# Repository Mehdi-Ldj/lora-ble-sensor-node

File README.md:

# Off-Grid Agricultural LoRa/BLE Sensor Node — Rev A

A 55 mm round, four-layer sensor node that runs from a solar cell and a 14500
LiFePO4 cell: 868 MHz LoRa, 2.4 GHz BLE, and an environmental sensor suite on
one board.

## Design viewer

| Schematic | Board |
|:---:|:---:|
| [Schematic, six pages (PDF)](docs/renders/schematic-rev-a.pdf) | [Open the project in KiCanvas][kicanvas] |

KiCanvas loads the whole project in the browser: the board opens first, and the
five sheets are one click away in its Project panel. No KiCad installation
required. The PDF is the quickest way to read the schematic end to end.

[kicanvas]: https://kicanvas.org/?repo=https%3A%2F%2Fgithub.com%2FMehdi-Ldj%2Flora-ble-sensor-node%2Ftree%2Fmain%2Fhardware%2Frev-a

## Overview

The node is meant to sit in a field and report microclimate data for months at a
time without a battery change. A solar harvester tops up a single LiFePO4 cell,
a boost holds 3.3 V, and the MCU wakes to sample temperature, humidity and soil
moisture before transmitting over LoRa.

Three choices shaped the board more than anything else:

- The radio is split. A bare nRF52840 runs BLE from a PCB antenna, while an
  SX1262 carries the long-range link through a U.FL connector, so the 868 MHz
  front end can be measured and re-matched without touching the MCU.
- The MCU is a bare aQFN73 at 0.4 mm pitch, fanned out directly on the top
  layer. No module, no fanout board.
- The RF feed is impedance-controlled. The 868 MHz path, the 2.4 GHz antenna
  feed and the U.FL launch all run in a 50 Ω net class over an In1.Cu plane, on
  a stackup chosen for that geometry.

The outline is the last constraint: Ø55 mm, three mounting holes, and an antenna
keepout that no layer may cross.

## Features

- **868 MHz** LoRa, discrete SX1262 with a switchless match/filter/balun and a
  U.FL measurement point
- **2.4 GHz** BLE from a bare **nRF52840** (aQFN73) with an on-board PCB antenna
- **BQ25570** solar harvester with PMOS reverse-polarity protection and TVS
- **TPS61099** 3.3 V boost from a single-cell 14500 LiFePO4
- Battery PTC, reverse-polarity protection, current-measure jumper and NTC divider
- **BME280** environment sensor and a switched analog soil probe
- SWD debug header, six test points, three fiducials
- 96 parts across five hierarchical sheets

## Board specifications

| Item | Value |
|---|---|
| Board size | **Ø 55.0 mm**, 4 layers |
| Stackup | **JLC04161H-7628**, FR4, Er 4.6, 1.6 mm nominal |
| Copper | 1 oz outer and inner, ENIG finish, green mask, white silk |
| Minimum feature | 0.20 mm track, 0.15 mm clearance, 0.20 mm drill |
| Vias | 0.30/0.20 mm and 0.20/0.20 mm, tented, no blind or buried |
| Impedance | 50 Ω ±10 % single-ended, In1.Cu reference |
| Assembly | JLCPCB Standard PCBA, 2 prototypes |

## Architecture

Line colour and weight separate the five signal classes: power, digital, analog,
RF and control. The 3V3 bus feeds the radio and the sensing block from the same
boost converter, and the soil probe is switched so it draws nothing while the
node sleeps.

## Design notes

### 868 MHz feed

The radio sheet carries a switchless match, filter and balun between the SX1262
and the U.FL, laid out as a 50 Ω coplanar waveguide over the In1.Cu ground plane.
The geometry was chosen from a quasi-static 2D sweep before layout:

| W (mm) | S (mm) | h (mm) | Z₀ (Ω) | εeff |
|---:|---:|---:|---:|---:|
| 0.38 | 0.20 | 0.210 | **50.4** | 3.51 |

The sweep and its caveats are in
[`simulation/results/cpw_sweep.md`](simulation/results/cpw_sweep.md). The
full-wave model and the VNA coupon are still to be run.

### 2.4 GHz antenna

The PCB antenna sits in a keepout with no copper on any layer, fed from the
nRF52840 through the same 50 Ω class. The keepout is the fragile part, and it is
documented with the stackup in [`docs/stackup.md`](docs/stackup.md).

### Power

The BQ25570 runs as a boost charger only — its buck converter is deliberately
unused — feeding a single LiFePO4 cell through a PTC and a reverse-polarity
PMOS. The TPS61099 then holds 3.3 V for the MCU, radio and sensors, and the soil
probe is switched so it cannot leak current while the node sleeps. The full pin
list and the reviewed net table are in the schematic.

### Package and assembly

Four layers carry the aQFN73 fanout on the top, a solid ground below it, and the
supplies on the inner layers. Assembly is Standard PCBA with X-ray, because the
aQFN73 and the BME280 both have pads underneath.

## Layout

| Front copper | Back copper |
|:---:|:---:|
|  |  |
| **Inner 1 — ground plane** | **Inner 2 — power** |
|  |  |

## Repository structure

| Path | Contents |
|---|---|
| `hardware/rev-a/` | KiCad 10 project: five schematic sheets, PCB, symbol and footprint libraries, 3D models |
| `simulation/` | Coplanar-waveguide pre-check for the 868 MHz feed, and the plan for the 3D model |
| `docs/` | [Assembly](docs/assembly-notes.md), [fabrication](docs/fab-notes.md) and [PCBA](docs/pcba-notes.md) notes, [stackup](docs/stackup.md), [impedance](docs/impedance.md), schematic PDF |
| `firmware/` | Reserved for the node firmware |

Open the project with KiCad 10:

```bash
kicad hardware/rev-a/lora-node.kicad_pro
```

## Fabrication and assembly

The board is drawn for JLCPCB 4-layer fabrication and Standard PCBA, with X-ray
inspection for the aQFN73 and BME280. Paste, stencil and panel choices are in
[`docs/fab-notes.md`](docs/fab-notes.md),
[`docs/assembly-notes.md`](docs/assembly-notes.md) and
[`docs/pcba-notes.md`](docs/pcba-notes.md).

The fabrication package for a release — gerbers, drill file, job file, BOM and
CPL — is attached to the release rather than committed here.

## Status

**Rev A is frozen and has not been fabricated yet.** The design is complete
through DRC, ERC and schematic/board parity.

## Licence

Released under the [CERN Open Hardware Licence Version 2 – Permissive](LICENSE).

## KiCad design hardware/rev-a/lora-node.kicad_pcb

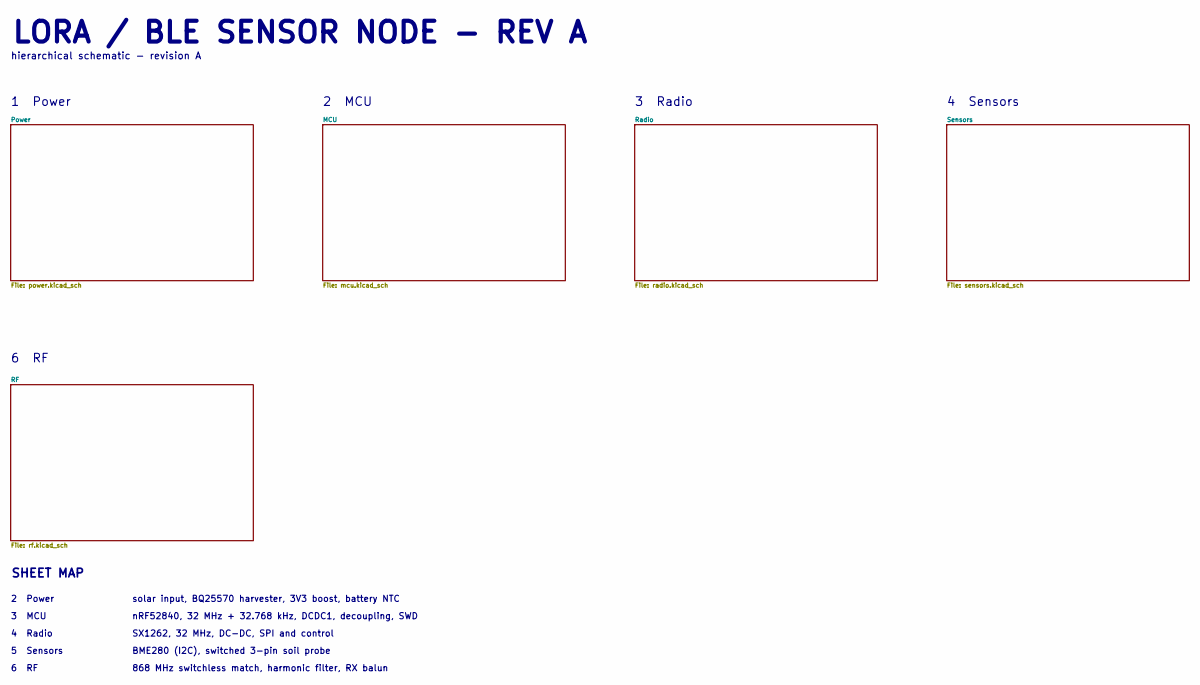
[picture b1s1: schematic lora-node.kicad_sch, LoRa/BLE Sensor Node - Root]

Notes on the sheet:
5 Sensors
4 Radio
2 MCU
3 MCU
2 Power
6 RF
SHEET MAP
BME280 (I2C), switched 3-pin soil probe
SX1262, 32 MHz, DC-DC, SPI and control
hierarchical schematic - revision A
LORA / BLE SENSOR NODE - REV A
1 Power
solar input, BQ25570 harvester, 3V3 boost, battery NTC
3 Radio
868 MHz switchless match, harmonic filter, RX balun
4 Sensors
nRF52840, 32 MHz + 32.768 kHz, DCDC1, decoupling, SWD

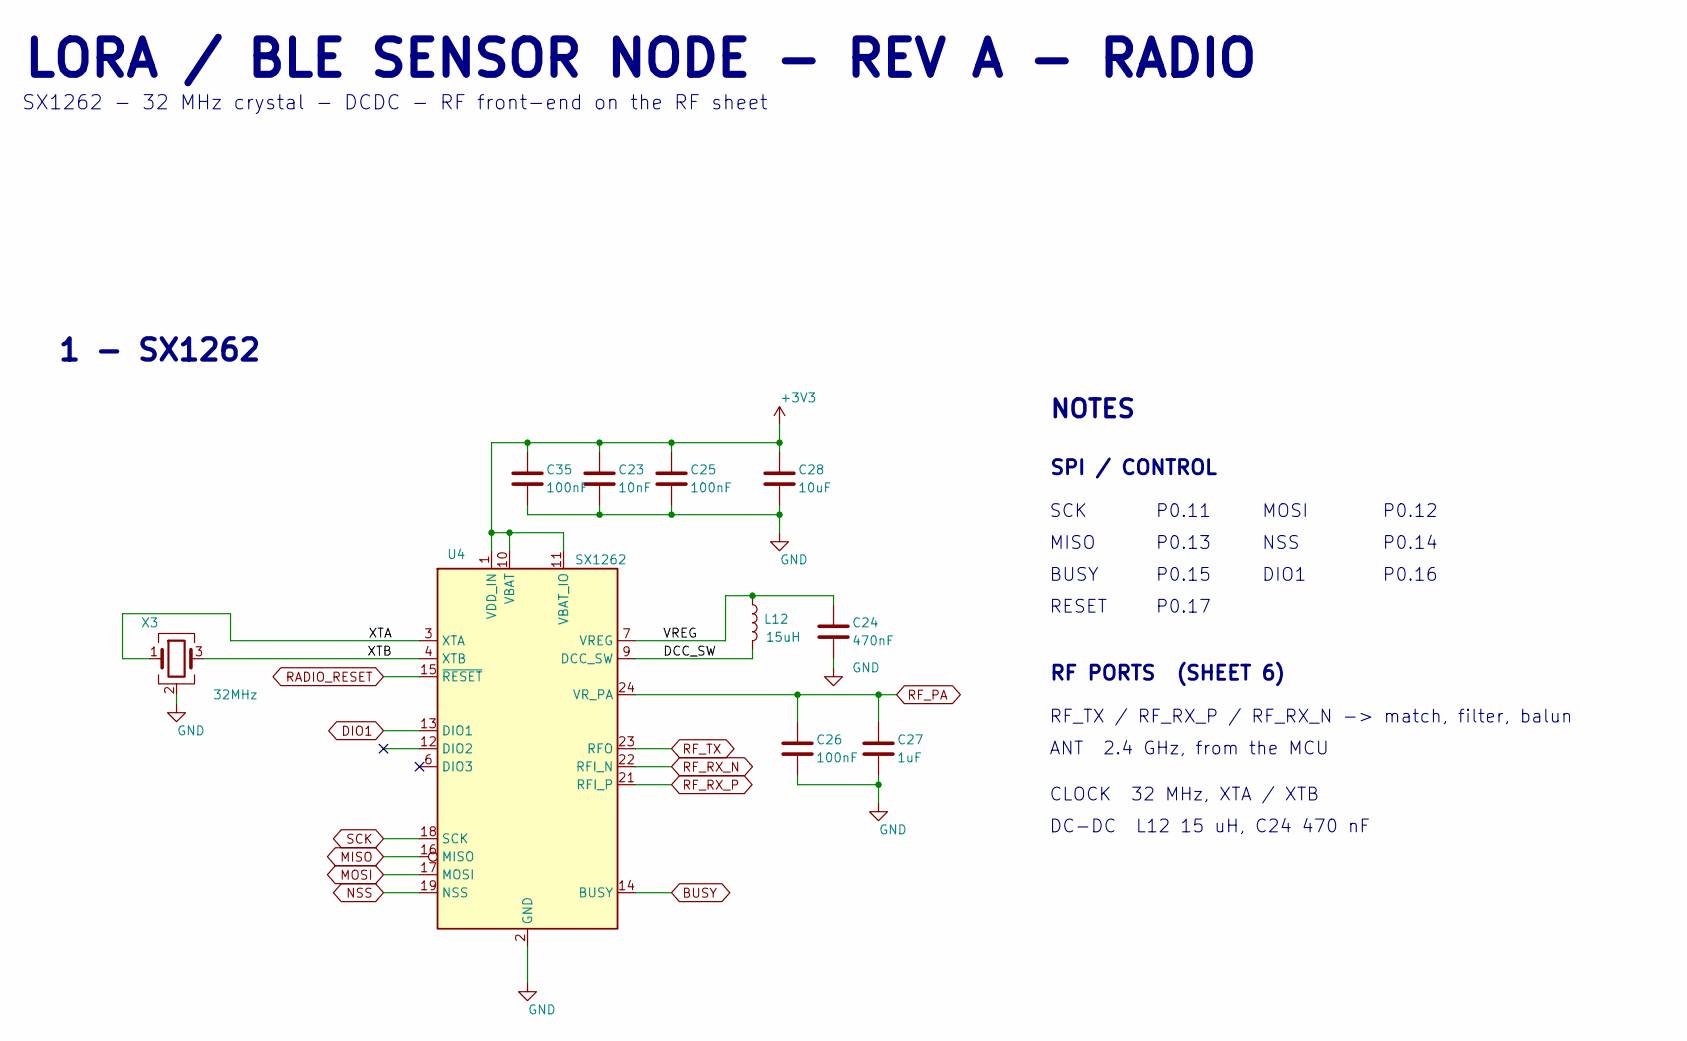
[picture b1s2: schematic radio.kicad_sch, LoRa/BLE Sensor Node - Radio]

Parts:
C23: 10nF; C_0402_1005Metric; MPN CL05B103KB5NNNC; LCSC C15195
C24: 470nF; C_0402_1005Metric; MPN CL05A474KP5NNNC; LCSC C47339
C25, C26, C35: 100nF; C_0402_1005Metric; MPN CL05B104KO5NNNC; LCSC C1525
C27: 1uF; C_0603_1608Metric; MPN CL10B105KA8NNNC; LCSC C29936
C28: 10uF; C_0805_2012Metric; MPN CL21A106KAYNNNE; LCSC C15850
L12: 15uH; L_0603_1608Metric; MPN MGFL1608F150MT-LF; LCSC C486329
U4: SX1262; QFN-24-1EP_4x4mm_P0.5mm_EP2.6x2.6mm; MPN SX1262IMLTRT; LCSC C191341
X3: 32MHz; Crystal_SMD_2016-4Pin_2.0x1.6mm; MPN ECS-320-10-37B-CKY-TR; LCSC C2450496

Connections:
+3V3: C23.1, C25.1, C28.1, C35.1, U4.1 (VDD_IN), U4.10 (VBAT), U4.11 (VBAT_IO); also elsewhere on the board
/Radio/DCC_SW: L12.2, U4.9 (DCC_SW)
/Radio/VREG: C24.1, L12.1, U4.7 (VREG)
/Radio/XTA: U4.3 (XTA), X3.1
/Radio/XTB: U4.4 (XTB), X3.3
BUSY: U4.14 (BUSY); also elsewhere on the board
DIO1: U4.13 (DIO1); also elsewhere on the board
GND: C23.2, C24.2, C25.2, C26.2, C27.2, C28.2, C35.2, U4.2 (GND), U4.5 (GND), U4.8 (GND), U4.20 (GND), U4.25 (GND), X3.2 (G), X3.4 (G); also elsewhere on the board
MISO: U4.16 (MISO); also elsewhere on the board
MOSI: U4.17 (MOSI); also elsewhere on the board
NSS: U4.19 (NSS); also elsewhere on the board
RADIO_RESET: U4.15 (~RESET); also elsewhere on the board
RF_PA: C26.1, C27.1, U4.24 (VR_PA); also elsewhere on the board
RF_RX_N: U4.22 (RFI_N); also elsewhere on the board
RF_RX_P: U4.21 (RFI_P); also elsewhere on the board
RF_TX: U4.23 (RFO); also elsewhere on the board
SCK: U4.18 (SCK); also elsewhere on the board

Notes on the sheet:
SPI / CONTROL
P0.11
DIO1
RF PORTS (SHEET 6)
1 - SX1262
CLOCK 32 MHz, XTA / XTB
DC-DC L12 15 uH, C24 470 nF
NSS
NOTES
BUSY
MOSI
LORA / BLE SENSOR NODE - REV A - RADIO
P0.16
SCK
SX1262 - 32 MHz crystal - DCDC - RF front-end on the RF sheet
P0.17
RF_TX / RF_RX_P / RF_RX_N -> match, filter, balun
P0.15
RESET
ANT 2.4 GHz, from the MCU
P0.12
P0.13
MISO
P0.14

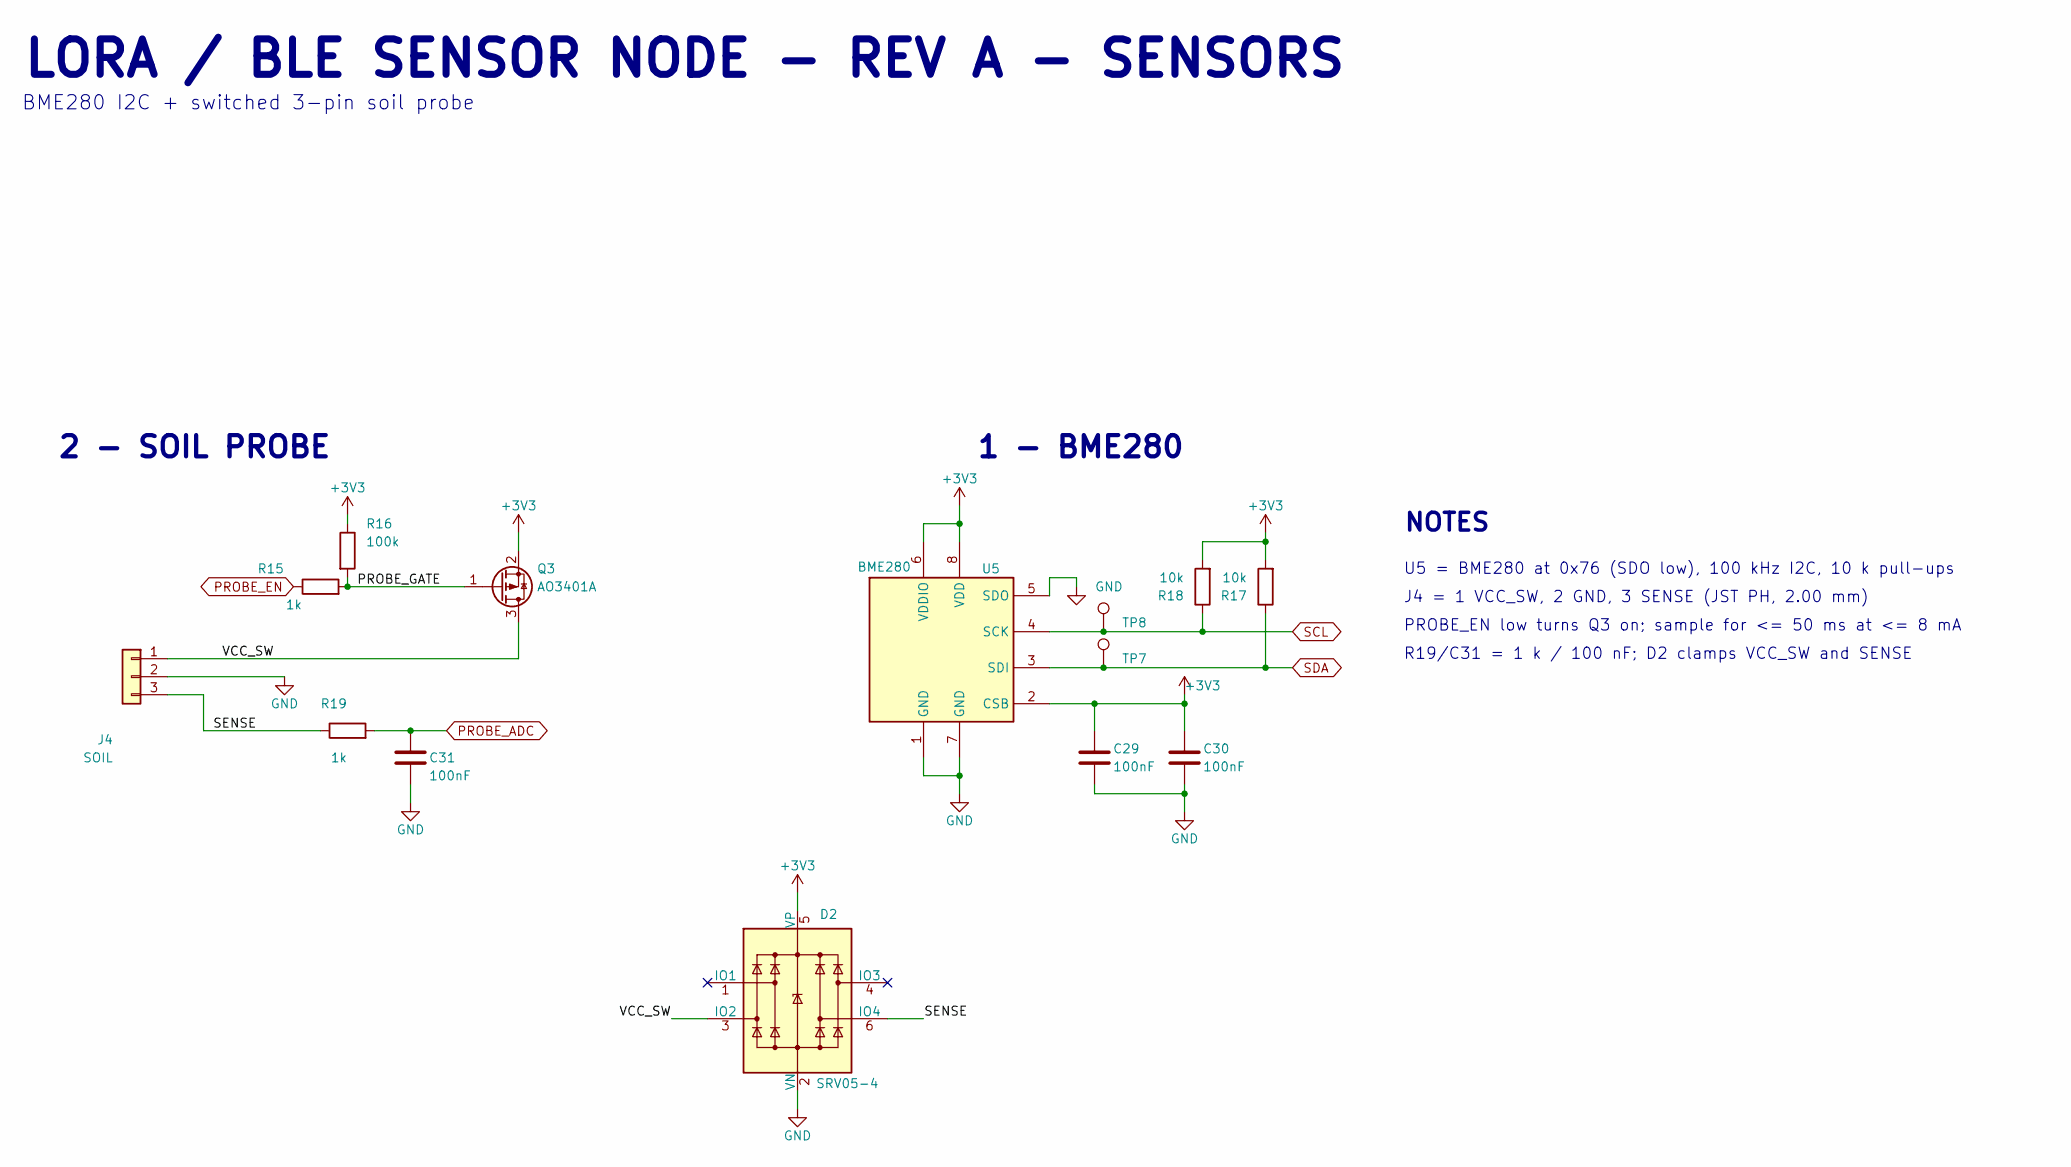
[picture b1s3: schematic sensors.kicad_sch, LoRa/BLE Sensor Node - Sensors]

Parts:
C29, C30, C31: 100nF; C_0402_1005Metric; MPN CL05B104KO5NNNC; LCSC C1525
D2: SRV05-4; SOT-23-6; MPN SRV05-4.TCT; LCSC C13612
J4: SOIL; JST_PH_B3B-PH-K_1x03_P2.00mm_Vertical; MPN B3B-PH-K-S(LF)(SN); LCSC C131339
Q3: AO3401A; SOT-23; MPN AO3401A; LCSC C15127
R15, R19: 1k; R_0402_1005Metric; MPN 0402WGF1001TCE; LCSC C11702
R16: 100k; R_0402_1005Metric; MPN 0402WGF1003TCE; LCSC C25741
R17, R18: 10k; R_0402_1005Metric; MPN RC0402FR-0710KL; LCSC C60490
TP7: SDA; TestPoint_Pad_D1.0mm
TP8: SCL; TestPoint_Pad_D1.0mm
U5: BME280; Bosch_LGA-8_2.5x2.5mm_P0.65mm_ClockwisePinNumbering; MPN BME280; LCSC C92489

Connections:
+3V3: C29.1, C30.1, D2.5 (VP), Q3.2 (S), R16.1, R17.2, R18.2, U5.2 (CSB), U5.6 (VDDIO), U5.8 (VDD); also elsewhere on the board
/Sensors/PROBE_GATE: Q3.1 (G), R15.2, R16.2
/Sensors/SENSE: D2.6 (IO4), J4.3, R19.1
/Sensors/VCC_SW: D2.3 (IO2), J4.1, Q3.3 (D)
GND: C29.2, C30.2, C31.2, D2.2 (VN), J4.2, U5.1 (GND), U5.5 (SDO), U5.7 (GND); also elsewhere on the board
PROBE_ADC: C31.1, R19.2; also elsewhere on the board
PROBE_EN: R15.1; also elsewhere on the board
SCL: R18.1, TP8.1 (1_1), U5.4 (SCK); also elsewhere on the board
SDA: R17.1, TP7.1 (1_1), U5.3 (SDI); also elsewhere on the board

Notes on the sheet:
J4 = 1 VCC_SW, 2 GND, 3 SENSE (JST PH, 2.00 mm)
LORA / BLE SENSOR NODE - REV A - SENSORS
BME280 I2C + switched 3-pin soil probe
1 - BME280
NOTES
U5 = BME280 at 0x76 (SDO low), 100 kHz I2C, 10 k pull-ups
2 - SOIL PROBE
PROBE_EN low turns Q3 on; sample for <= 50 ms at <= 8 mA
R19/C31 = 1 k / 100 nF; D2 clamps VCC_SW and SENSE

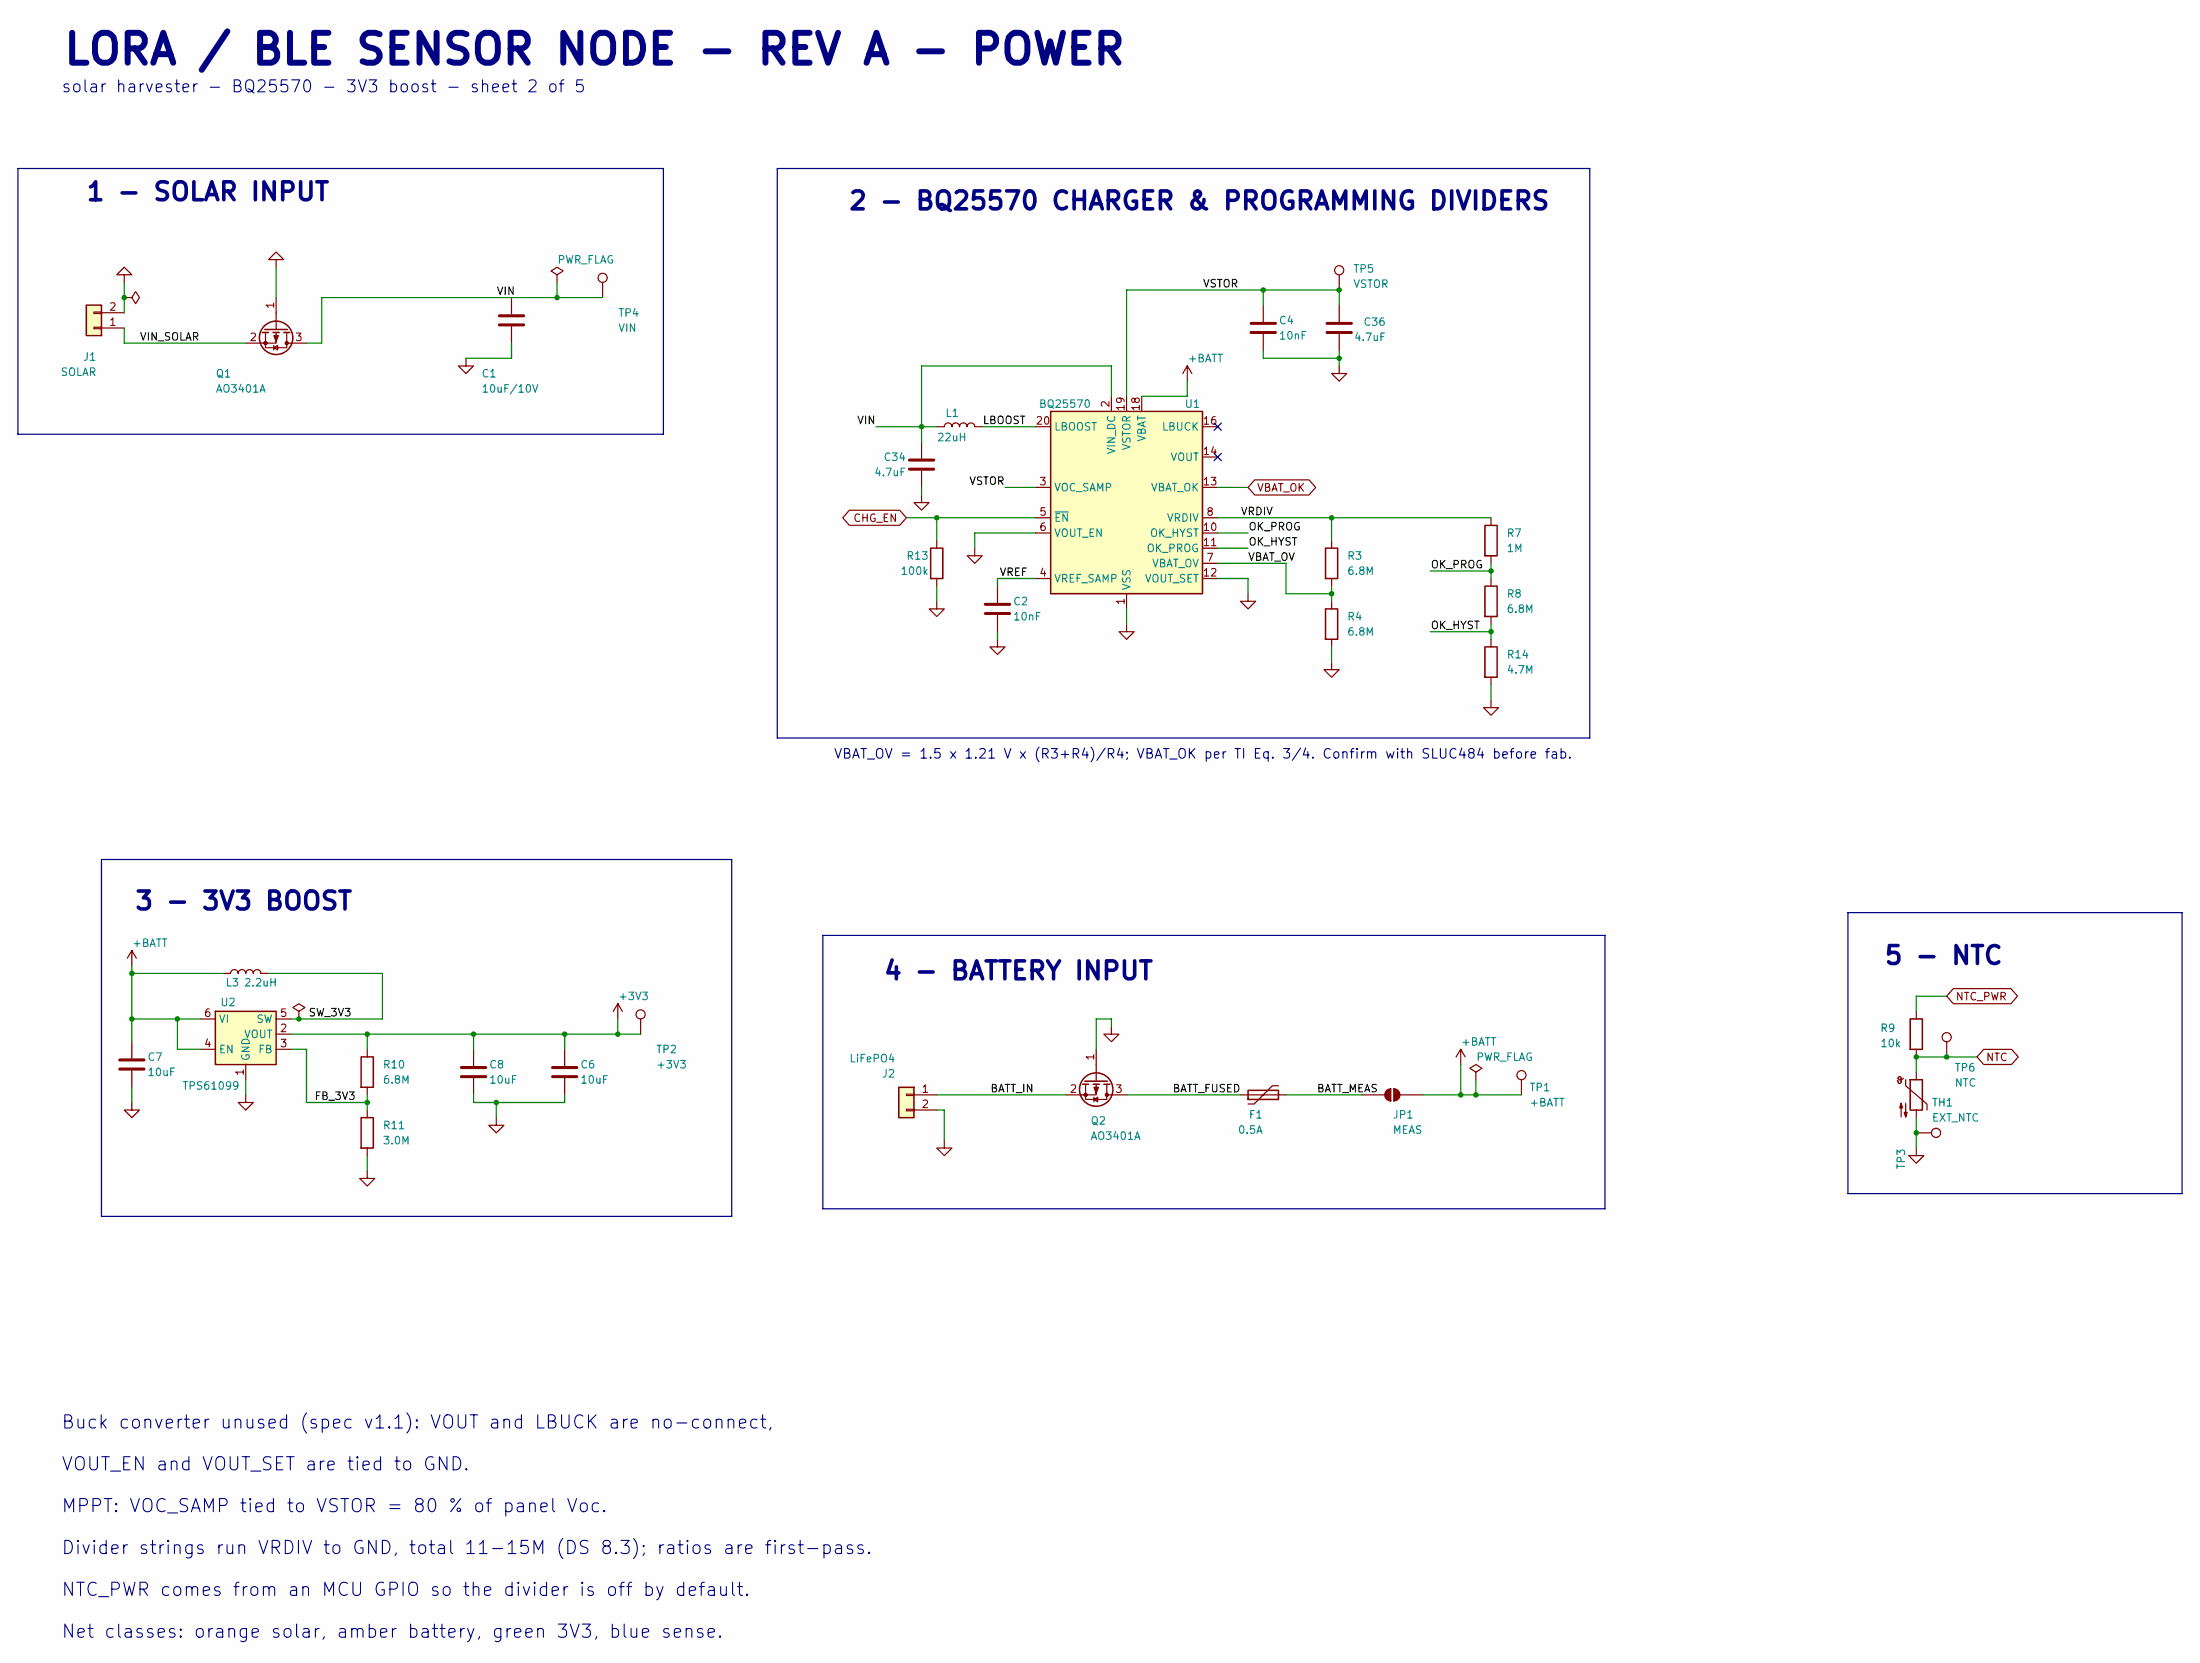
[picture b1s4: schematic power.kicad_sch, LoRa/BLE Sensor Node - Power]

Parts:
C1: 10uF/10V; C_0805_2012Metric; MPN CL21A106KAYNNNE; LCSC C15850
C2, C4: 10nF; C_0402_1005Metric; MPN CL05B103KB5NNNC; LCSC C15195
C6, C7, C8: 10uF; C_0805_2012Metric; MPN CL21A106KAYNNNE; LCSC C15850
C34, C36: 4.7uF; C_0603_1608Metric; MPN CL10A475KO8NNNC; LCSC C19666
F1: 0.5A; Fuse_1812_4532Metric; MPN SMD1812P050TF/30; LCSC C12559
J1: SOLAR; JST_PH_B2B-PH-K_1x02_P2.00mm_Vertical; MPN B2B-PH-K-S(LF)(SN); LCSC C131337
J2: LiFePO4; JST_PH_B2B-PH-K_1x02_P2.00mm_Vertical; MPN B2B-PH-K-S(LF)(SN); LCSC C131337
JP1: MEAS; PinHeader_1x02_P2.54mm_Vertical; MPN PZ254V-11-02P; LCSC C492401
L1: 22uH; L_1210_3225Metric; MPN CBC3225T220KR; LCSC C223225
L3: 2.2uH; L_1210_3225Metric; MPN DFE322512F-2R2M=P2; LCSC C3222669
Q1, Q2: AO3401A; SOT-23; MPN AO3401A; LCSC C15127
R3, R4, R8, R10: 6.8M; R_0402_1005Metric; MPN RC0402FR-076M8L; LCSC C477777
R7: 1M; R_0402_1005Metric; MPN 0402WGF1004TCE; LCSC C26083
R9: 10k; R_0402_1005Metric; MPN RC0402FR-0710KL; LCSC C60490
R11: 3.0M; R_0402_1005Metric; MPN 0402WGF3004TCE; LCSC C56582
R13: 100k; R_0402_1005Metric; MPN 0402WGF1003TCE; LCSC C25741
R14: 4.7M; R_0402_1005Metric; MPN 0402WGF4704TCE; LCSC C474132
TH1: EXT_NTC; JST_XH_B2B-XH-A_1x02_P2.50mm_Vertical; MPN B2B-XH-A(LF)(SN); LCSC C158012
TP1: +BATT; TestPoint_Pad_D1.0mm
TP2: +3V3; TestPoint_Pad_D1.0mm
TP3: TestPoint_Pad_D1.0mm
TP4: VIN; TestPoint_Pad_D1.0mm
TP5: VSTOR; TestPoint_Pad_D1.0mm
TP6: NTC; TestPoint_Pad_D1.0mm
U1: BQ25570; QFN-20-1EP_3.5x3.5mm_P0.5mm_EP2x2mm; MPN BQ25570RGRR; LCSC C506250
U2: TPS61099; WSON-6-1EP_2x2mm_P0.65mm_EP1x1.6mm; MPN TPS61099DRVR; LCSC C2842395

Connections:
+3V3: C6.1, C8.1, R10.1, TP2.1 (1_1), U2.2 (VOUT); also elsewhere on the board
+BATT: C7.1, JP1.2 (B), L3.1, TP1.1 (1_1), U1.18 (VBAT), U2.4 (EN), U2.6 (VI)
/Power/BATT_FUSED: F1.1, Q2.3 (D)
/Power/BATT_IN: J2.1, Q2.2 (S)
/Power/BATT_MEAS: F1.2, JP1.1 (A)
/Power/FB_3V3: R10.2, R11.1, U2.3 (FB)
/Power/LBOOST: L1.2, U1.20 (LBOOST)
/Power/OK_HYST: R8.2, R14.1, U1.11 (OK_PROG)
/Power/OK_PROG: R7.2, R8.1, U1.10 (OK_HYST)
/Power/SW_3V3: L3.2, U2.5 (SW)
/Power/VBAT_OV: R3.2, R4.1, U1.7 (VBAT_OV)
/Power/VIN: C1.1, C34.1, L1.1, Q1.3 (D), TP4.1 (1_1), U1.2 (VIN_DC)
/Power/VIN_SOLAR: J1.1, Q1.2 (S)
/Power/VRDIV: R3.1, R7.1, U1.8 (VRDIV)
/Power/VREF: C2.1, U1.4 (VREF_SAMP)
/Power/VSTOR: C4.1, C36.1, TP5.1 (1_1), U1.3 (VOC_SAMP), U1.19 (VSTOR)
CHG_EN: R13.1, U1.5 (~EN); also elsewhere on the board
GND: C1.2, C2.2, C4.2, C6.2, C7.2, C8.2, C34.2, C36.2, J1.2, J2.2, Q1.1 (G), Q2.1 (G), R4.2, R11.2, R13.2, R14.2, TH1.2, TP3.1 (1_1), U1.1 (VSS), U1.6 (VOUT_EN), U1.9 (VSS), U1.12 (VOUT_SET), U1.15 (VSS), U1.17 (VSS), U1.21 (VSS), U2.1 (GND), U2.7 (GND); also elsewhere on the board
NTC: R9.2, TH1.1, TP6.1 (1_1); also elsewhere on the board
NTC_PWR: R9.1; also elsewhere on the board
VBAT_OK: U1.13 (VBAT_OK); also elsewhere on the board

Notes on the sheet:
4 - BATTERY INPUT
Net classes: orange solar, amber battery, green 3V3, blue sense.
5 - NTC
Divider strings run VRDIV to GND, total 11-15M (DS 8.3); ratios are first-pass.
solar harvester - BQ25570 - 3V3 boost - sheet 2 of 5
VOUT_EN and VOUT_SET are tied to GND.
MPPT: VOC_SAMP tied to VSTOR = 80 % of panel Voc.
Buck converter unused (spec v1.1): VOUT and LBUCK are no-connect,
1 - SOLAR INPUT
3 - 3V3 BOOST
VBAT_OV = 1.5 x 1.21 V x (R3+R4)/R4; VBAT_OK per TI Eq. 3/4. Confirm with SLUC484 before fab.
LORA / BLE SENSOR NODE - REV A - POWER
NTC_PWR comes from an MCU GPIO so the divider is off by default.
2 - BQ25570 CHARGER & PROGRAMMING DIVIDERS

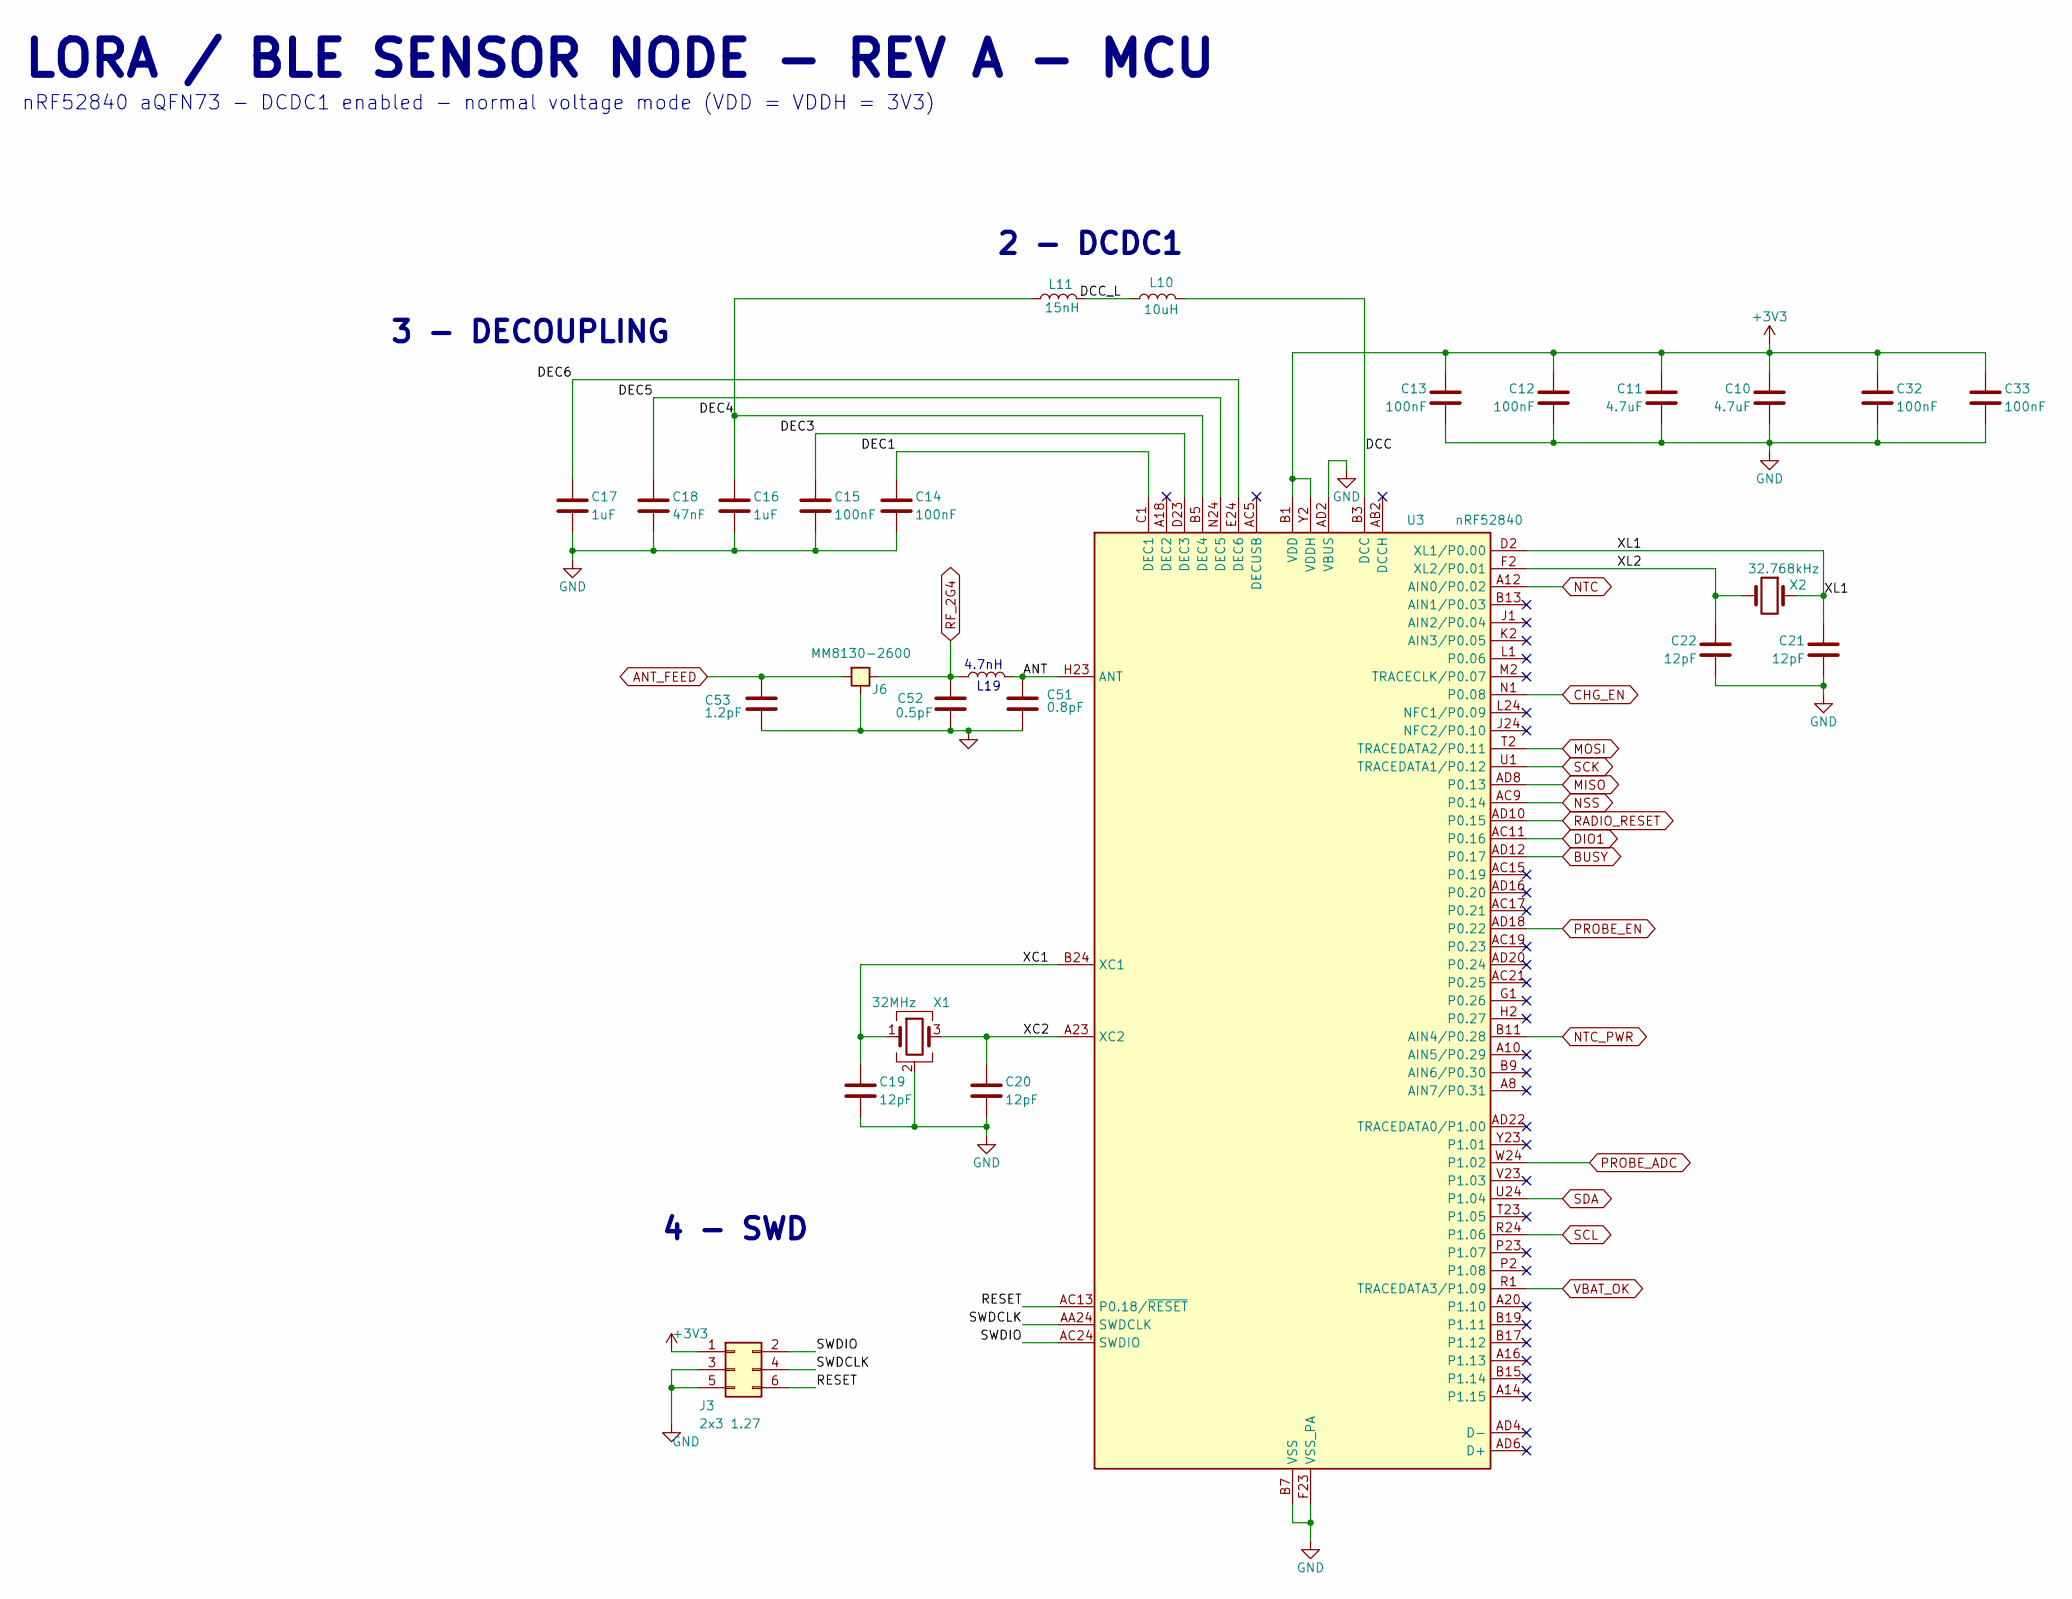
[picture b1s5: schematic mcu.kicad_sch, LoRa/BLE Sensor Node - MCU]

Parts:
C10, C11: 4.7uF; C_0603_1608Metric; MPN CL10A475KO8NNNC; LCSC C19666
C12, C13, C14, C15, C32, C33: 100nF; C_0402_1005Metric; MPN CL05B104KO5NNNC; LCSC C1525
C16, C17: 1uF; C_0603_1608Metric; MPN CL10B105KA8NNNC; LCSC C29936
C18: 47nF; C_0402_1005Metric; MPN CC0402KRX7R9BB473; LCSC C272875
C19, C20, C21, C22: 12pF; C_0402_1005Metric; MPN CC0402JRNPO9BN120; LCSC C106201
C51: 0.8pF; C_0402_1005Metric; MPN GJM1555C1HR80BB01D; LCSC C76915
C52: 0.5pF; C_0402_1005Metric; MPN GJM1555C1HR50BB01D; LCSC C76911
C53: 1.2pF; C_0402_1005Metric; MPN GJM1555C1H1R2WB01D; LCSC C76899
J3: 2x3 1.27; PinHeader_2x03_P1.27mm_Vertical_SMD; MPN PZ127-2-03-S; LCSC C3975186
J6: MM8130-2600; COAXIAL-SWF; MPN MM8130-2600RB8; LCSC C91633
L10: 10uH; L_0603_1608Metric; MPN MLZ1608N100LT000; LCSC C194437
L11: 15nH; L_0402_1005Metric; MPN LQW15AN15NG00D; LCSC C98055
L19: 4.7nH; L_0402_1005Metric; MPN LQW15AN4N7B00D; LCSC C98064
U3: nRF52840; Nordic_AQFN-73-1EP_7x7mm_P0.5mm; MPN NRF52840-QIAA-R; LCSC C190794
X1: 32MHz; Crystal_SMD_2016-4Pin_2.0x1.6mm; MPN TX201632M4BBCE2T; LCSC C5339095
X2: 32.768kHz; Crystal_SMD_3215-2Pin_3.2x1.5mm; MPN Q13FC13500003; LCSC C99010

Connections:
+3V3: C10.1, C11.1, C12.1, C13.1, C32.1, C33.1, J3.1, U3.A22 (VDD), U3.AD14 (VDD), U3.AD23 (VDD), U3.B1 (VDD), U3.W1 (VDD), U3.Y2 (VDDH); also elsewhere on the board
/MCU/ANT: C51.1, L19.2, U3.H23 (ANT)
/MCU/DCC: L10.1, U3.B3 (DCC)
/MCU/DCC_L: L10.2, L11.1
/MCU/DEC1: C14.1, U3.C1 (DEC1)
/MCU/DEC3: C15.1, U3.D23 (DEC3)
/MCU/DEC4: C16.1, L11.2, U3.B5 (DEC4)
/MCU/DEC5: C18.1, U3.N24 (DEC5)
/MCU/DEC6: C17.1, U3.E24 (DEC6)
/MCU/RESET: J3.6, U3.AC13 (P0.18/~RESET)
/MCU/SWDCLK: J3.4, U3.AA24 (SWDCLK)
/MCU/SWDIO: J3.2, U3.AC24 (SWDIO)
/MCU/XC1: C19.1, U3.B24 (XC1), X1.1
/MCU/XC2: C20.1, U3.A23 (XC2), X1.3
/MCU/XL1: C21.1, U3.D2 (XL1/P0.00), X2.1
/MCU/XL2: C22.1, U3.F2 (XL2/P0.01), X2.2
ANT_FEED: C53.1, J6.3 (ANT)
BUSY: U3.AD12 (P0.17); also elsewhere on the board
CHG_EN: U3.N1 (P0.08); also elsewhere on the board
DIO1: U3.AC11 (P0.16); also elsewhere on the board
GND: C10.2, C11.2, C12.2, C13.2, C14.2, C15.2, C16.2, C17.2, C18.2, C19.2, C20.2, C21.2, C22.2, C32.2, C33.2, C51.2, C52.2, C53.2, J3.3, J3.5, J6.2 (GND), U3.AD2 (VBUS), U3.B7 (VSS), U3.EP (VSS), U3.F23 (VSS_PA), X1.2 (G), X1.4 (G); also elsewhere on the board
MISO: U3.AD8 (P0.13); also elsewhere on the board
MOSI: U3.T2 (TRACEDATA2/P0.11); also elsewhere on the board
NSS: U3.AC9 (P0.14); also elsewhere on the board
NTC: U3.A12 (AIN0/P0.02); also elsewhere on the board
NTC_PWR: U3.B11 (AIN4/P0.28); also elsewhere on the board
PROBE_ADC: U3.W24 (P1.02); also elsewhere on the board
PROBE_EN: U3.AD18 (P0.22); also elsewhere on the board
RADIO_RESET: U3.AD10 (P0.15); also elsewhere on the board
RF_2G4: C52.1, J6.1 (RF), L19.1
SCK: U3.U1 (TRACEDATA1/P0.12); also elsewhere on the board
SCL: U3.R24 (P1.06); also elsewhere on the board
SDA: U3.U24 (P1.04); also elsewhere on the board
VBAT_OK: U3.R1 (TRACEDATA3/P1.09); also elsewhere on the board

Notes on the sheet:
2 - DCDC1
LORA / BLE SENSOR NODE - REV A - MCU
nRF52840 aQFN73 - DCDC1 enabled - normal voltage mode (VDD = VDDH = 3V3)
4 - SWD
L19
3 - DECOUPLING
4.7nH
